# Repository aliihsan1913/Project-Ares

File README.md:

# Project Ares

## Project Disclaimer & Purpose
This project is an engineering simulation created strictly for fun and entertainment. To be completely honest, no physical RF plasma generator has been manufactured, and this system is not intended for actual deployment. Everything presented here is a theoretical "what-if" scenario and a creative exercise in conceptual hardware design and software simulation. 

## Overview
Project Ares is a cyber-physical system (CPS) testbed designed to simulate a 13.56 MHz RF Plasma Generator for Inductively Coupled Plasma (ICP) applications. 

This repository contains the conceptual hardware design files for the high-power RF generator and the software source code for the simulation engine.

## Hardware Architecture (RF Power Stage)
The theoretical hardware component focuses on generating high voltage switching power while maintaining strict signal integrity and thermal management.

* **Switching Stage:** LMG1210 High-Speed GaN/MOSFET driver paired with Si7141DP power MOSFETs capable of handling 100V.
* **PCB Stack-up:** 4-layer FR-4 design. Power routing is buried in inner layers, and switching noise is shielded by a solid ground plane.
* **Thermal Management:** Extensive use of thermal vias under active components, utilizing the bottom layer as a massive passive heatsink.
* **Antenna Topology:** 50 Ohms impedance-matched Circular Planar Spiral Loop Antenna, designed to overcome the wavelength constraint of the 13.56 MHz ISM band.

### Hardware Visuals

## Software & Simulation
The software side consists of deterministic physics and visualization scripts running on Python and Pygame. **Please note that Artificial Intelligence was used to assist in writing and structuring the software code for this simulation.**

* **Autonomous Control:** A dynamic PID controller (Kp=0.55, Ki=0.08, Kd=0.12) adjusts the simulated RF Beam Current in real-time against chaotic solar flux data.
* **State Machine:** The system autonomously transitions between IDLE, STORM ALERT, OVERDRIVE, and CRITICAL FAILURE based on thermal limits and capacitor charge states.
* **Telemetry HUD:** Live data visualization for RF sync, cyclotron power, and system temperature.

### Simulation Visuals

## Repository Structure
The repository is organized into specific directories for hardware, software, and imagery. 

The hardware directory contains the KiCad project files, specifically `fp-info-cache`, `marssiklot.kicad_pcb`, `marssiklot.kicad_prl`, `marssiklot.kicad_pro`, and `marssiklot.kicad_sch`. 

The software directory contains the core simulation scripts, which include `cyclotrone.py`, `Aresgame.py`, and `Aressimu.py`.

```text
Ares/
├── Hardware/
│   ├── fp-info-cache
│   ├── marssiklot.kicad_pcb
│   ├── marssiklot.kicad_prl
│   ├── marssiklot.kicad_pro
│   └── marssiklot.kicad_sch
├── Images/
│   ├── Antenna.png
│   ├── CyclotroneSim.png
│   ├── Ares_RF.png
│   ├── Ares_RF_PCB.png
│   ├── SchemaAres.png
│   └── Sim_Screen.png
└── Software/
    ├── cyclotrone.py
    ├── Aresgame.py
    └── Aressimu.py

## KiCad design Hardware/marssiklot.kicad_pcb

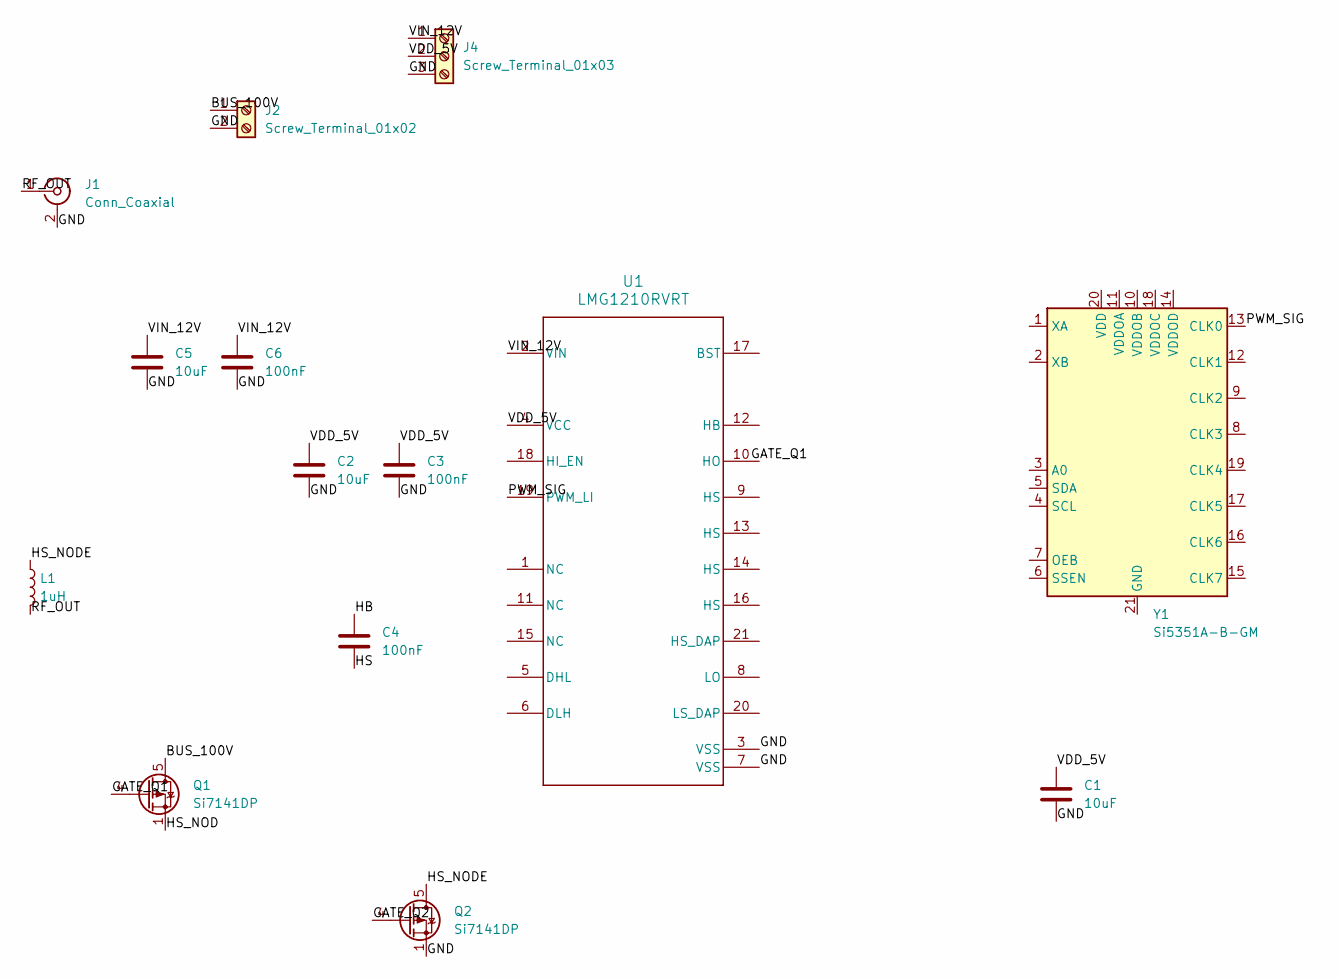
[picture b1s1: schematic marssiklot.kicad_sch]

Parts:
C1, C2, C5: 10uF; C_0805_2012Metric
C3, C4, C6: 100nF; C_0805_2012Metric
J1: Conn_Coaxial; SMA_Amphenol_132289_EdgeMount
J2: Screw_Terminal_01x02; TerminalBlock_Phoenix_MKDS-1,5-2_1x02_P5.00mm_Horizontal
J4: Screw_Terminal_01x03; TerminalBlock_Phoenix_MKDS-1,5-3_1x03_P5.00mm_Horizontal
L1: 1uH; L_1210_3225Metric
Q1, Q2: Si7141DP; PowerPAK_SO-8_Single
U1: LMG1210RVRT; QFN-20-1EP_4x4mm_P0.5mm_EP2.5x2.5mm
Y1: Si5351A-B-GM; QFN-20-1EP_4x4mm_P0.5mm_EP2.7x2.7mm

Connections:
/BUS_100V: J2.1, Q1.5 (D)
/GATE_Q1: Q1.4 (G)
/GATE_Q2: Q2.4 (G)
/GND: C1.2, C2.2, C3.2, C5.2, C6.2, J1.2 (Ext), J2.2, J4.3, Q2.1 (S), Q2.2 (S), Q2.3 (S), U1.3 (VSS), U1.7 (VSS)
/HB: C4.1
/HS: C4.2
/HS_NOD: Q1.1 (S), Q1.2 (S), Q1.3 (S)
/HS_NODE: L1.1, Q2.5 (D)
/PWM_SIG: U1.19 (PWM_LI), Y1.13 (CLK0)
/RF_OUT: J1.1 (In), L1.2
/VDD_5V: C1.1, C2.1, C3.1, J4.2, U1.4 (VCC)
/VIN_12V: C5.1, C6.1, J4.1, U1.2 (VIN)

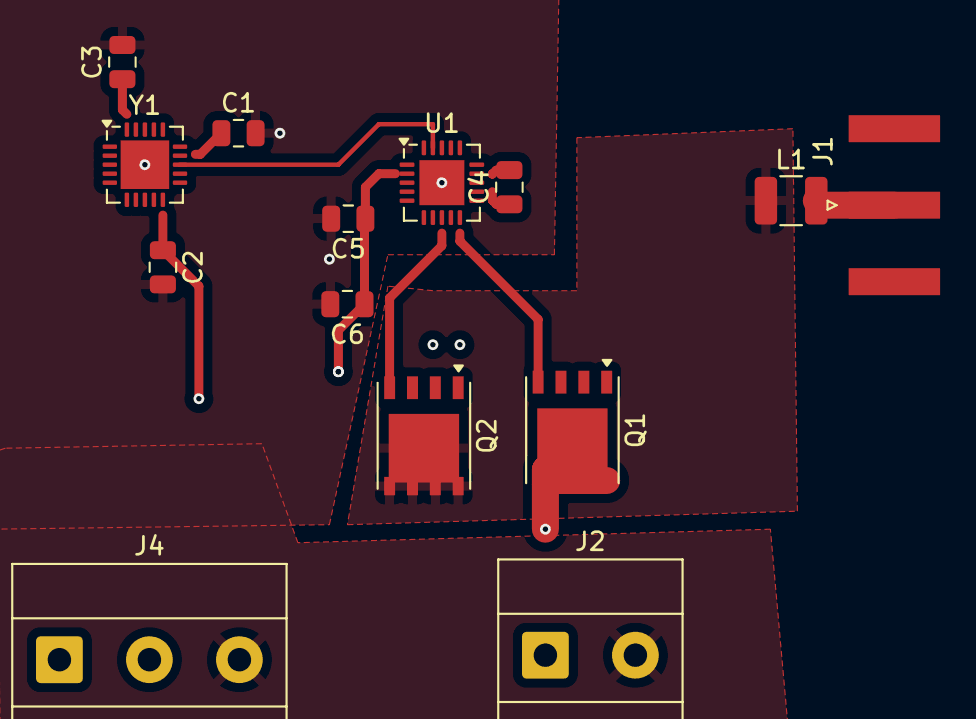
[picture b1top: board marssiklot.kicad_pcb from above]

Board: 4 copper layers, 14 parts (0 on the bottom side), 8 nets.
